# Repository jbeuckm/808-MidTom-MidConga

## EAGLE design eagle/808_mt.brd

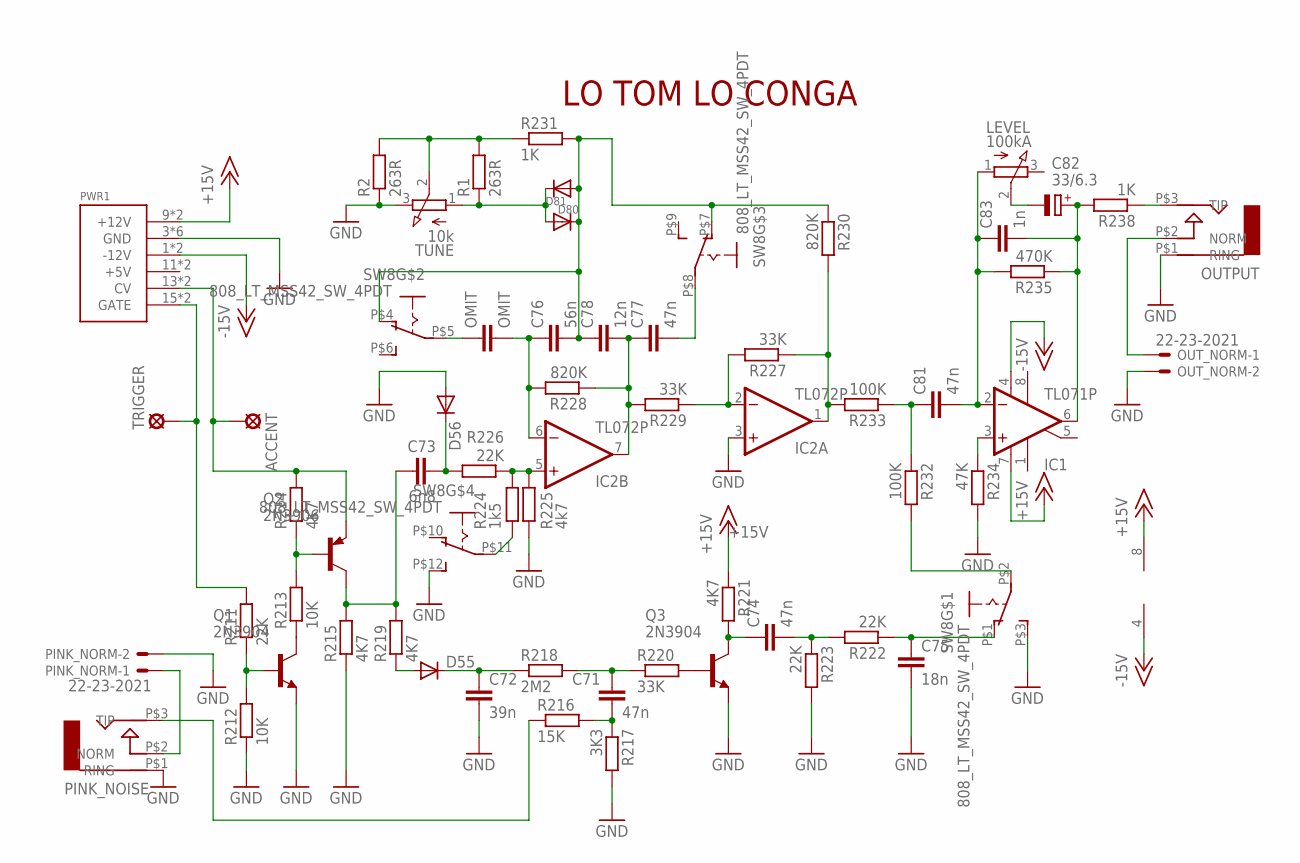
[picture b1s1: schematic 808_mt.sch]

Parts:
ACCENT: LSP10
C71, C74, C77, C81: 47n; C050-024X044
C72: 39n; C050-024X044
C73: 6n8; C035-030X60
C75: 18n; C035-030X60
C76: 56n; C050-024X044
C78: 12n; C035-025X75
C82: 33/6.3; E2-5
C83: 1n; C035-025X75
D55, D56, D80, D81: DIODEDO-1N4148; DO-1N4148
IC1: TL071P; DIL08
IC2: TL072P; DIL08
LEVEL: 100kA; 3RP/1610N
OMIT: OMIT; C050-024X044
OUTPUT: AUDIO-JACK; ERTHENVAR-JACK-90DEG
OUT_NORM: 22-23-2021
PINK_NOISE: AUDIO-JACK; ERTHENVAR-JACK-90DEG
PINK_NORM: 22-23-2021
PWR1: POWER; POWER_16
Q1, Q3: 2N3904; TO92
Q2: 2N3906; TO92
R1, R2: 263R; 0207/7
R211, R222, R223, R226: 22K; 0207/7
R212, R213: 10K; 0207/7
R214, R215, R219, R221: 4K7; 0207/7
R216: 15K; 0207/7
R217: 3K3; 0207/7
R218: 2M2; 0207/7
R220, R227, R229: 33K; 0207/7
R224: 1k5; 0207/7
R225: 4k7; 0207/7
R228, R230: 820K; 0207/7
R231, R238: 1K; 0207/7
R232, R233: 100K; 0207/7
R234: 47K; 0207/7
R235: 470K; 0207/7
SW8: 808_LT_MSS42_SW_4PDT; 808_LT_MSS42_SW_SLIDE
TRIGGER: LSP10
TUNE: 10k; 3RP/1610N

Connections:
+15V: IC1.7 (V+), IC2.8 (V+), PWR1.9 (+12V), PWR1.10 (+12V), R221.1
-15V: IC1.4 (V-), IC2.4 (V-), PWR1.1 (-12V), PWR1.2 (-12V)
GND: C72.2, C75.P$2 (2), D56.A, IC2.3 (+IN), OUTPUT.P$1 (RING), OUT_NORM.2, PINK_NOISE.P$1 (RING), PINK_NORM.2, PWR1.3 (GND), PWR1.4 (GND), PWR1.5 (GND), PWR1.6 (GND), PWR1.7 (GND), PWR1.8 (GND), Q1.3 (E), Q3.3 (E), R2.1, R212.1, R215.1, R217.2, R223.2, R225.1, R234.2, SW8.P$3 (S), SW8.P$12 (S), TUNE.3 (E)
LT: PWR1.15 (GATE), PWR1.16 (GATE), R211.2, TRIGGER.MP
LT_LC_OUT: OUTPUT.P$3 (TIP), R238.1
unnamed: Q3.2 (B), R220.2
unnamed: Q1.1 (C), R213.1
unnamed: OUTPUT.P$2 (NORM), OUT_NORM.1
unnamed: PINK_NOISE.P$2 (NORM), PINK_NORM.1
unnamed: OMIT.1, SW8.P$5
unnamed: IC2.5 (+IN), R224.2, R225.2, R226.1
unnamed: IC1.3 (+IN), R234.1
unnamed: R224.1, SW8.P$11
unnamed: Q2.2 (B), R213.2, R214.1
unnamed: Q1.2 (B), R211.1, R212.2
unnamed: C73.P$1 (1), Q2.1 (C), R215.2, R219.2
unnamed: D55.A, R219.1
unnamed: C73.P$2 (2), D56.C, R226.2
unnamed: C76.2, C78.P$1 (1), D80.A, D81.C, R230.1, R231.2, SW8.P$4 (O), SW8.P$7 (O)
unnamed: C76.1, IC2.6 (-IN), OMIT.2, R228.2
unnamed: C77.1, C78.P$2 (2), IC2.7 (OUT), R228.1, R229.2
unnamed: D80.C, D81.A, R1.1, TUNE.1 (A)
unnamed: R1.2, R2.2, R231.1, TUNE.2 (S)
unnamed: IC2.2 (-IN), R227.2, R229.1
unnamed: IC2.1 (OUT), R227.1, R230.2, R233.2
unnamed: C81.1, R232.1, R233.1
unnamed: C81.2, C83.P$1 (1), IC1.2 (-IN), LEVEL.1 (A), R235.2
unnamed: C82.-, LEVEL.2 (S)
unnamed: C82.+, C83.P$2 (2), IC1.6 (OUT), R235.1, R238.2
unnamed: C74.1, Q3.1 (C), R221.2
unnamed: C75.P$1 (1), R222.1, SW8.P$1 (O)
unnamed: C71.2, R216.2, R217.1
unnamed: C71.1, R218.2, R220.1
unnamed: C72.1, D55.C, R218.1
unnamed: C77.2, SW8.P$8
unnamed: R232.2, SW8.P$2
unnamed: C74.2, R222.2, R223.1
PN: PINK_NOISE.P$3 (TIP), R216.1
TRIG: ACCENT.MP, PWR1.13 (CV), PWR1.14 (CV), Q2.3 (E), R214.2

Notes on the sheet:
LO TOM LO CONGA

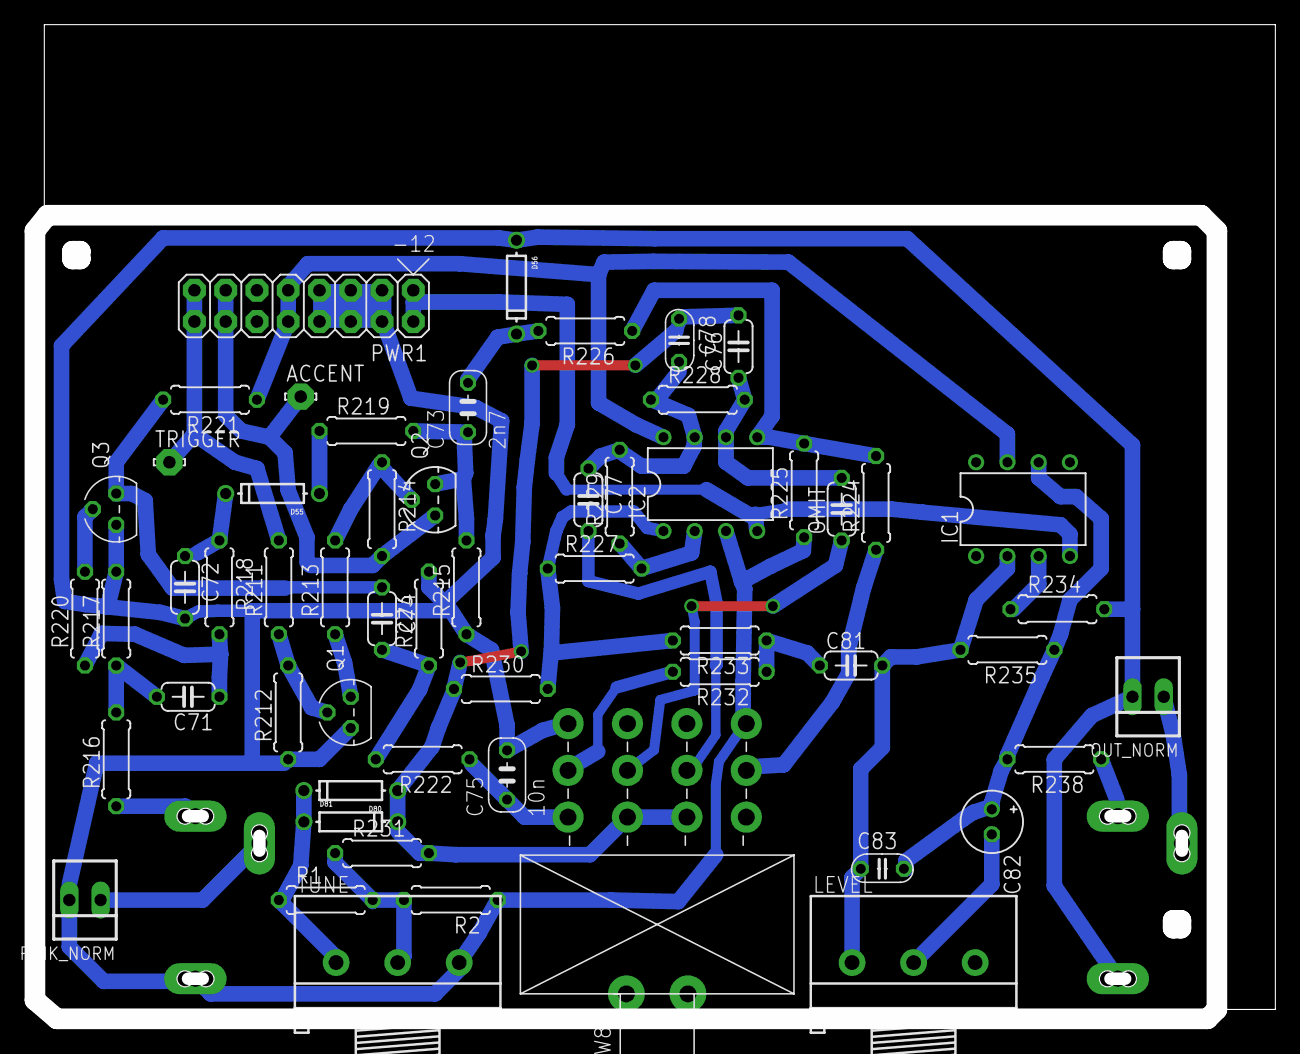
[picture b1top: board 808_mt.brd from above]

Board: 2 copper layers, 100.8 x 80.8 mm, 59 parts (0 on the bottom side), 39 nets.

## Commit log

2016-04-18 renaming to 808_mt
2016-04-19 gcode
2016-04-23 changed values for hitom
2016-05-12 panel
2016-06-06 values for low tom
2018-06-01 adjust values visible and render layout image
